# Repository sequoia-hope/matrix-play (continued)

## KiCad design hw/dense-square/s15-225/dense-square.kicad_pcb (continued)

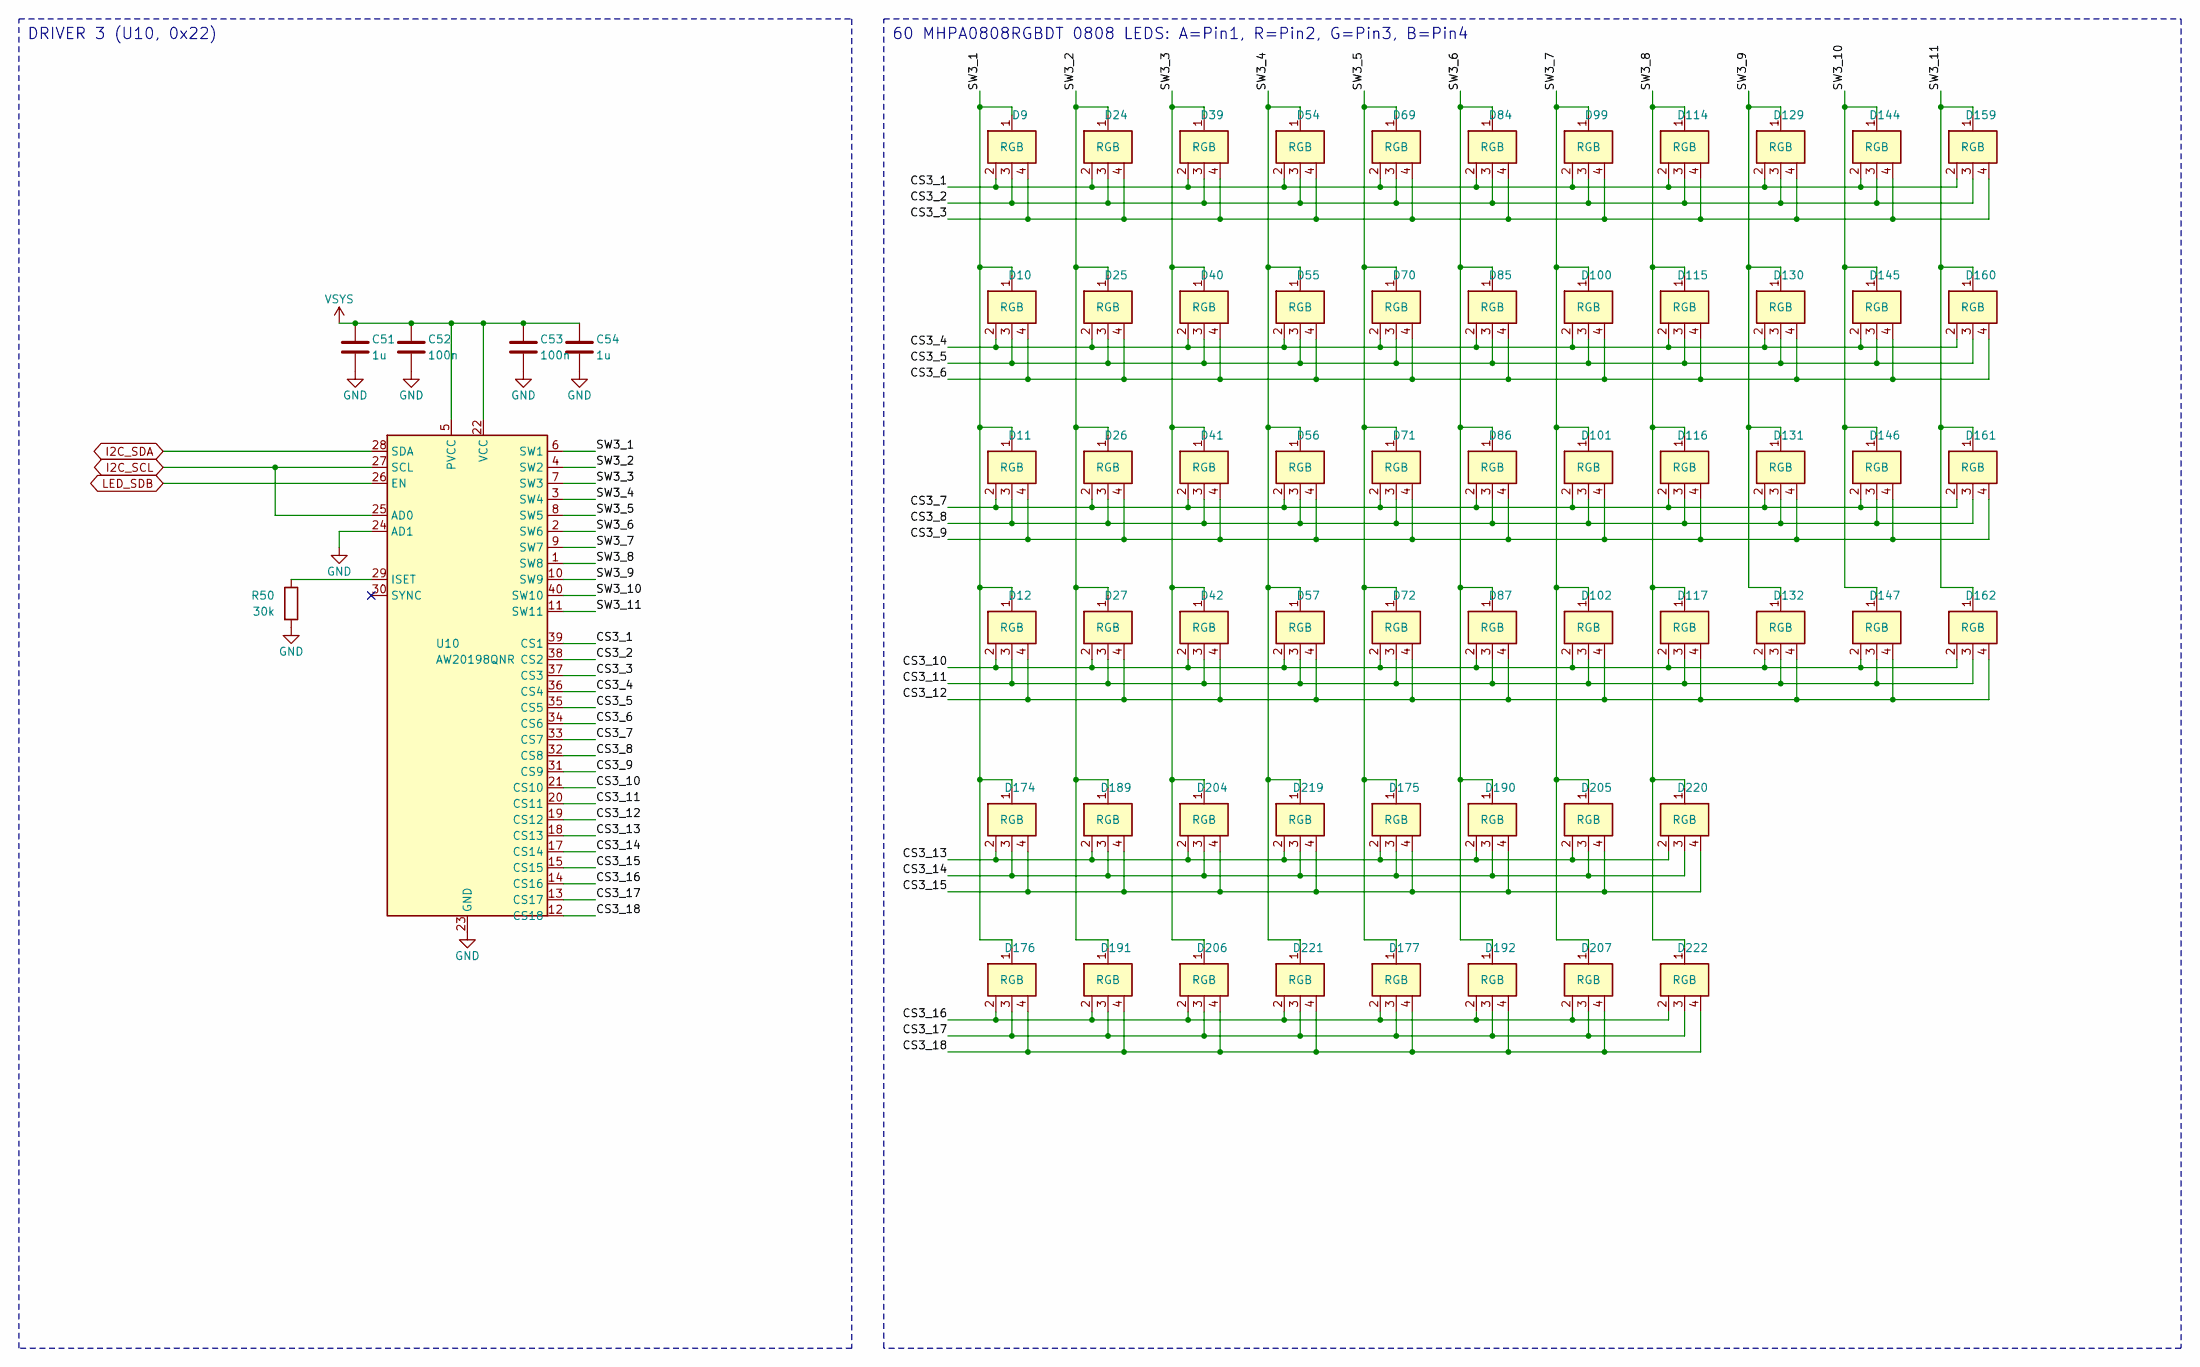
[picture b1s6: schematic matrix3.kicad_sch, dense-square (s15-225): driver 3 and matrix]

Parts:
C51, C54: 1u; C_0402_1005Metric; MPN CL05A105KA5NQNC; LCSC C52923
C52, C53: 100n; C_0402_1005Metric; MPN CL05B104KO5NNNC; LCSC C1525
D9, D10, D11, D12, D24, D25, D26, D27, D39, D40, D41, D42, D54, D55, D56, D57, D69, D70, D71, D72, D84, D85, D86, D87, D99, D100, D101, D102, D114, D115, D116, D117, D129, D130, D131, D132, D144, D145, D146, D147, D159, D160, D161, D162, D174, D175, D176, D177, D189, D190, D191, D192, D204, D205, D206, D207, D219, D220, D221, D222: RGB; LED_MHPA0808RGBDT; MPN MHPA0808RGBDT; LCSC C404279
R50: 30k; R_0402_1005Metric; MPN 0402WGF3002TCE; LCSC C25776
U10: AW20198QNR; AW20198_QFN-40-1EP_5x5mm_P0.4mm_EP3.4x3.4mm; MPN AW20198QNR; LCSC C5137654

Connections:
/Driver 3 and matrix/CS3_1: D9.2 (R), D24.2 (R), D39.2 (R), D54.2 (R), D69.2 (R), D84.2 (R), D99.2 (R), D114.2 (R), D129.2 (R), D144.2 (R), D159.2 (R), U10.39 (CS1)
/Driver 3 and matrix/CS3_2: D9.3 (G), D24.3 (G), D39.3 (G), D54.3 (G), D69.3 (G), D84.3 (G), D99.3 (G), D114.3 (G), D129.3 (G), D144.3 (G), D159.3 (G), U10.38 (CS2)
/Driver 3 and matrix/CS3_3: D9.4 (B), D24.4 (B), D39.4 (B), D54.4 (B), D69.4 (B), D84.4 (B), D99.4 (B), D114.4 (B), D129.4 (B), D144.4 (B), D159.4 (B), U10.37 (CS3)
/Driver 3 and matrix/CS3_4: D10.2 (R), D25.2 (R), D40.2 (R), D55.2 (R), D70.2 (R), D85.2 (R), D100.2 (R), D115.2 (R), D130.2 (R), D145.2 (R), D160.2 (R), U10.36 (CS4)
/Driver 3 and matrix/CS3_5: D10.3 (G), D25.3 (G), D40.3 (G), D55.3 (G), D70.3 (G), D85.3 (G), D100.3 (G), D115.3 (G), D130.3 (G), D145.3 (G), D160.3 (G), U10.35 (CS5)
/Driver 3 and matrix/CS3_6: D10.4 (B), D25.4 (B), D40.4 (B), D55.4 (B), D70.4 (B), D85.4 (B), D100.4 (B), D115.4 (B), D130.4 (B), D145.4 (B), D160.4 (B), U10.34 (CS6)
/Driver 3 and matrix/CS3_7: D11.2 (R), D26.2 (R), D41.2 (R), D56.2 (R), D71.2 (R), D86.2 (R), D101.2 (R), D116.2 (R), D131.2 (R), D146.2 (R), D161.2 (R), U10.33 (CS7)
/Driver 3 and matrix/CS3_8: D11.3 (G), D26.3 (G), D41.3 (G), D56.3 (G), D71.3 (G), D86.3 (G), D101.3 (G), D116.3 (G), D131.3 (G), D146.3 (G), D161.3 (G), U10.32 (CS8)
/Driver 3 and matrix/CS3_9: D11.4 (B), D26.4 (B), D41.4 (B), D56.4 (B), D71.4 (B), D86.4 (B), D101.4 (B), D116.4 (B), D131.4 (B), D146.4 (B), D161.4 (B), U10.31 (CS9)
/Driver 3 and matrix/CS3_10: D12.2 (R), D27.2 (R), D42.2 (R), D57.2 (R), D72.2 (R), D87.2 (R), D102.2 (R), D117.2 (R), D132.2 (R), D147.2 (R), D162.2 (R), U10.21 (CS10)
/Driver 3 and matrix/CS3_11: D12.3 (G), D27.3 (G), D42.3 (G), D57.3 (G), D72.3 (G), D87.3 (G), D102.3 (G), D117.3 (G), D132.3 (G), D147.3 (G), D162.3 (G), U10.20 (CS11)
/Driver 3 and matrix/CS3_12: D12.4 (B), D27.4 (B), D42.4 (B), D57.4 (B), D72.4 (B), D87.4 (B), D102.4 (B), D117.4 (B), D132.4 (B), D147.4 (B), D162.4 (B), U10.19 (CS12)
/Driver 3 and matrix/CS3_13: D174.2 (R), D175.2 (R), D189.2 (R), D190.2 (R), D204.2 (R), D205.2 (R), D219.2 (R), D220.2 (R), U10.18 (CS13)
/Driver 3 and matrix/CS3_14: D174.3 (G), D175.3 (G), D189.3 (G), D190.3 (G), D204.3 (G), D205.3 (G), D219.3 (G), D220.3 (G), U10.17 (CS14)
/Driver 3 and matrix/CS3_15: D174.4 (B), D175.4 (B), D189.4 (B), D190.4 (B), D204.4 (B), D205.4 (B), D219.4 (B), D220.4 (B), U10.15 (CS15)
/Driver 3 and matrix/CS3_16: D176.2 (R), D177.2 (R), D191.2 (R), D192.2 (R), D206.2 (R), D207.2 (R), D221.2 (R), D222.2 (R), U10.14 (CS16)
/Driver 3 and matrix/CS3_17: D176.3 (G), D177.3 (G), D191.3 (G), D192.3 (G), D206.3 (G), D207.3 (G), D221.3 (G), D222.3 (G), U10.13 (CS17)
/Driver 3 and matrix/CS3_18: D176.4 (B), D177.4 (B), D191.4 (B), D192.4 (B), D206.4 (B), D207.4 (B), D221.4 (B), D222.4 (B), U10.12 (CS18)
/Driver 3 and matrix/SW3_1: D9.1 (A), D10.1 (A), D11.1 (A), D12.1 (A), D174.1 (A), D176.1 (A), U10.6 (SW1)
/Driver 3 and matrix/SW3_2: D24.1 (A), D25.1 (A), D26.1 (A), D27.1 (A), D189.1 (A), D191.1 (A), U10.4 (SW2)
/Driver 3 and matrix/SW3_3: D39.1 (A), D40.1 (A), D41.1 (A), D42.1 (A), D204.1 (A), D206.1 (A), U10.7 (SW3)
/Driver 3 and matrix/SW3_4: D54.1 (A), D55.1 (A), D56.1 (A), D57.1 (A), D219.1 (A), D221.1 (A), U10.3 (SW4)
/Driver 3 and matrix/SW3_5: D69.1 (A), D70.1 (A), D71.1 (A), D72.1 (A), D175.1 (A), D177.1 (A), U10.8 (SW5)
/Driver 3 and matrix/SW3_6: D84.1 (A), D85.1 (A), D86.1 (A), D87.1 (A), D190.1 (A), D192.1 (A), U10.2 (SW6)
/Driver 3 and matrix/SW3_7: D99.1 (A), D100.1 (A), D101.1 (A), D102.1 (A), D205.1 (A), D207.1 (A), U10.9 (SW7)
/Driver 3 and matrix/SW3_8: D114.1 (A), D115.1 (A), D116.1 (A), D117.1 (A), D220.1 (A), D222.1 (A), U10.1 (SW8)
/Driver 3 and matrix/SW3_9: D129.1 (A), D130.1 (A), D131.1 (A), D132.1 (A), U10.10 (SW9)
/Driver 3 and matrix/SW3_10: D144.1 (A), D145.1 (A), D146.1 (A), D147.1 (A), U10.40 (SW10)
/Driver 3 and matrix/SW3_11: D159.1 (A), D160.1 (A), D161.1 (A), D162.1 (A), U10.11 (SW11)
I2C_SCL: U10.25 (AD0), U10.27 (SCL); also elsewhere on the board
I2C_SDA: U10.28 (SDA); also elsewhere on the board
LED_SDB: U10.26 (EN); also elsewhere on the board
unnamed: R50.1, U10.29 (ISET)
VSYS: C51.1, C52.1, C53.1, C54.1, U10.5 (PVCC), U10.22 (VCC); also elsewhere on the board

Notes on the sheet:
DRIVER 3 (U10, 0x22)
60 MHPA0808RGBDT 0808 LEDS: A=Pin1, R=Pin2, G=Pin3, B=Pin4

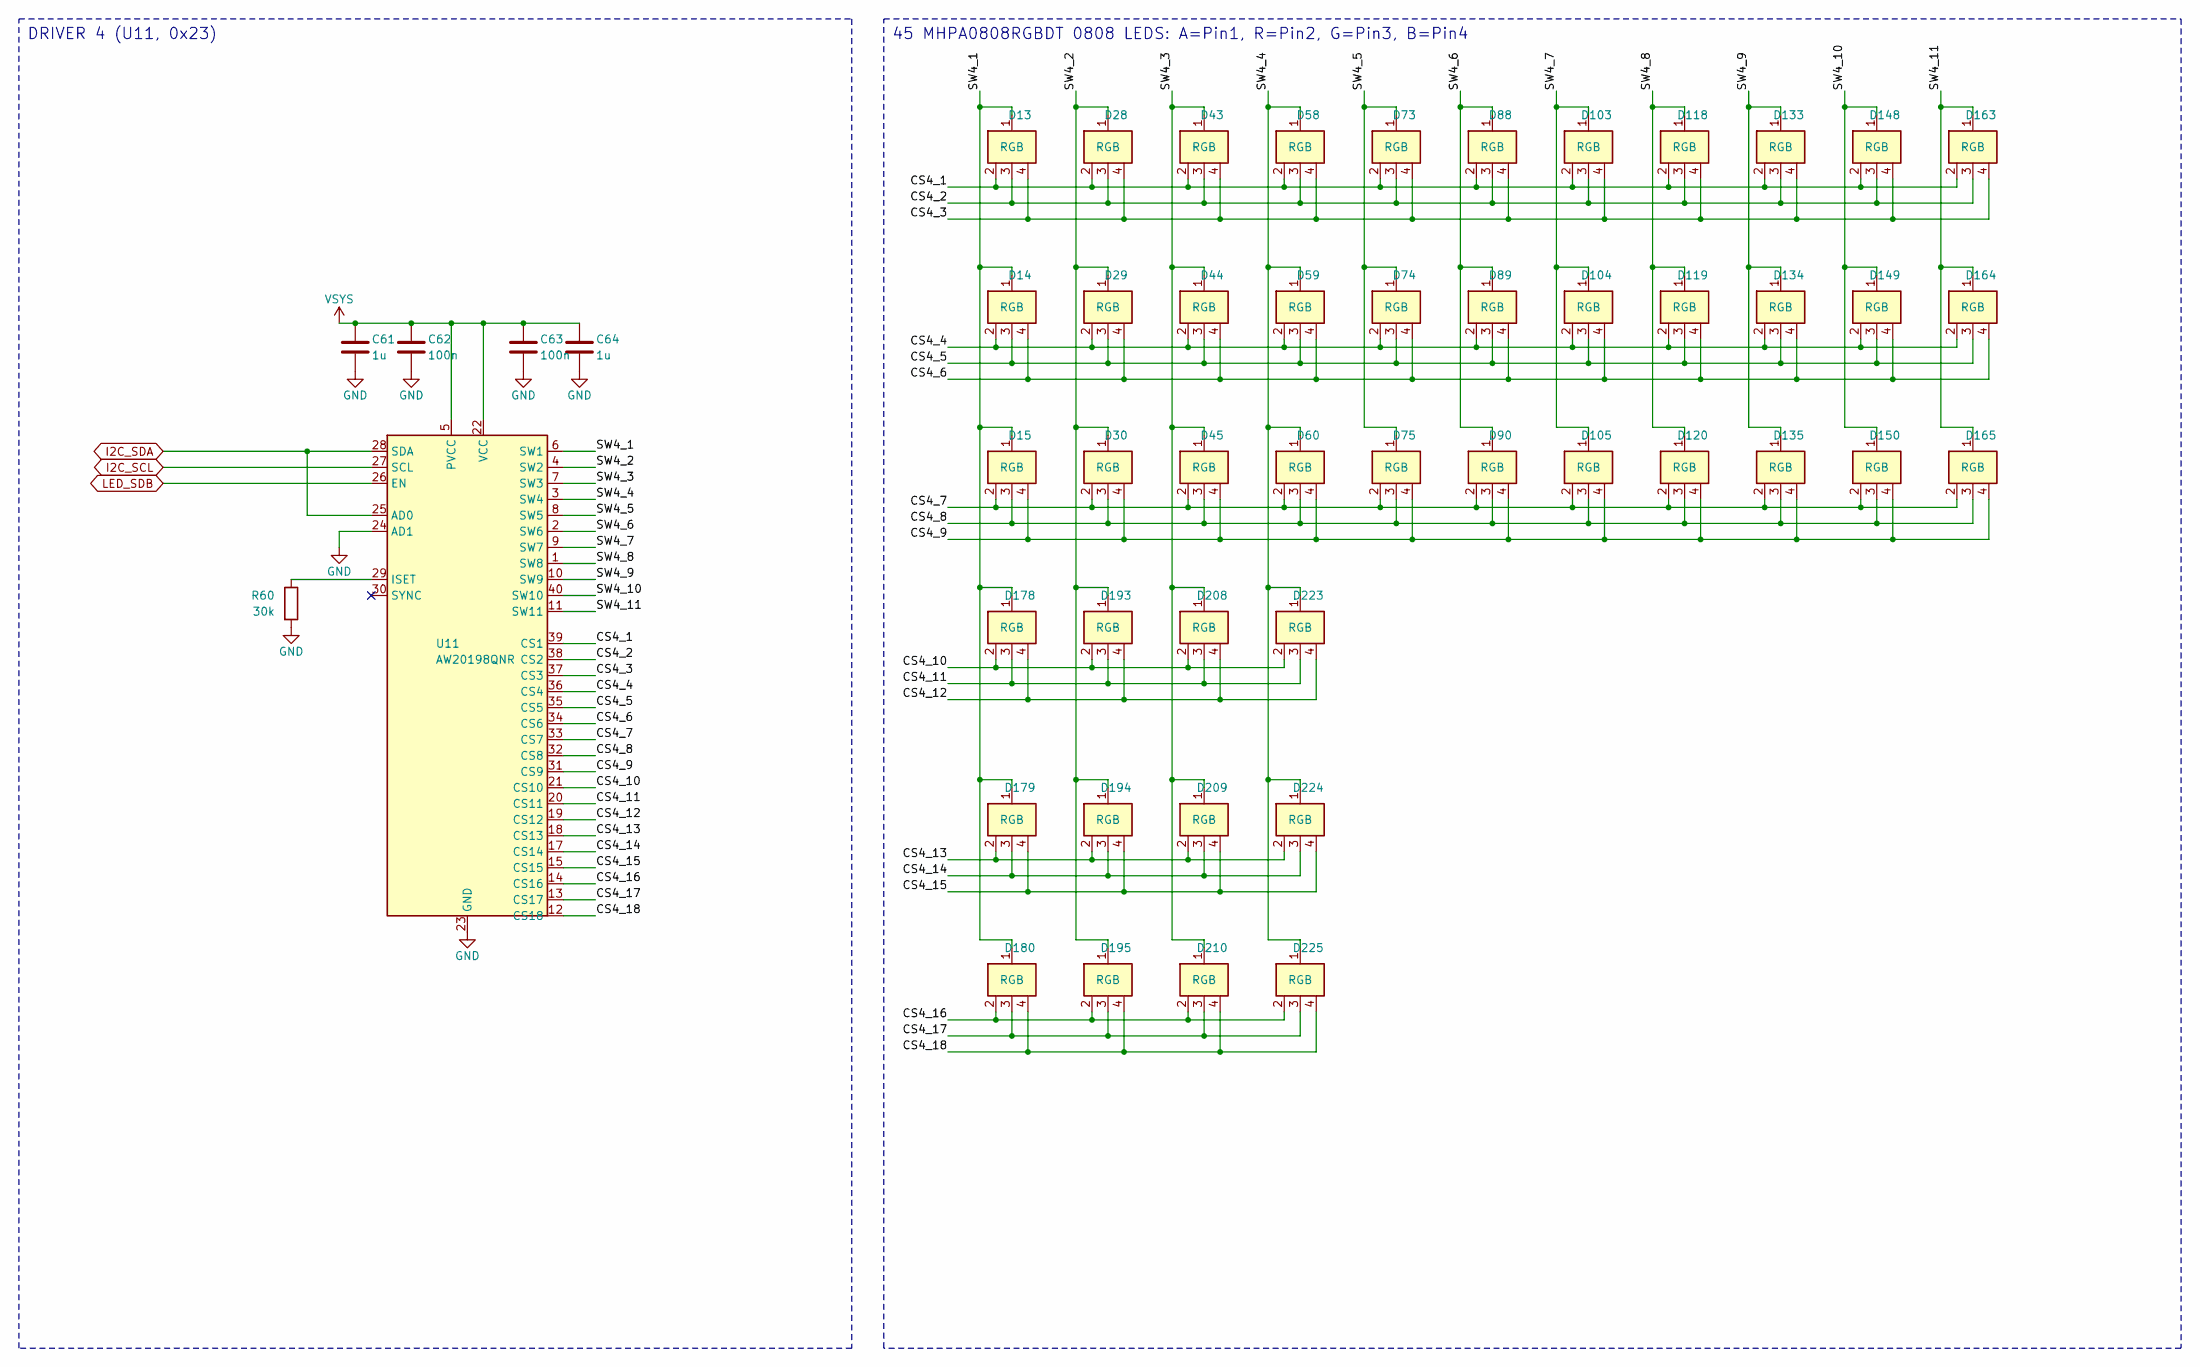
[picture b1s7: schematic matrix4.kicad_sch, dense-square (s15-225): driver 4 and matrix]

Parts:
C61, C64: 1u; C_0402_1005Metric; MPN CL05A105KA5NQNC; LCSC C52923
C62, C63: 100n; C_0402_1005Metric; MPN CL05B104KO5NNNC; LCSC C1525
D13, D14, D15, D28, D29, D30, D43, D44, D45, D58, D59, D60, D73, D74, D75, D88, D89, D90, D103, D104, D105, D118, D119, D120, D133, D134, D135, D148, D149, D150, D163, D164, D165, D178, D179, D180, D193, D194, D195, D208, D209, D210, D223, D224, D225: RGB; LED_MHPA0808RGBDT; MPN MHPA0808RGBDT; LCSC C404279
R60: 30k; R_0402_1005Metric; MPN 0402WGF3002TCE; LCSC C25776
U11: AW20198QNR; AW20198_QFN-40-1EP_5x5mm_P0.4mm_EP3.4x3.4mm; MPN AW20198QNR; LCSC C5137654

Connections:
/Driver 4 and matrix/CS4_1: D13.2 (R), D28.2 (R), D43.2 (R), D58.2 (R), D73.2 (R), D88.2 (R), D103.2 (R), D118.2 (R), D133.2 (R), D148.2 (R), D163.2 (R), U11.39 (CS1)
/Driver 4 and matrix/CS4_2: D13.3 (G), D28.3 (G), D43.3 (G), D58.3 (G), D73.3 (G), D88.3 (G), D103.3 (G), D118.3 (G), D133.3 (G), D148.3 (G), D163.3 (G), U11.38 (CS2)
/Driver 4 and matrix/CS4_3: D13.4 (B), D28.4 (B), D43.4 (B), D58.4 (B), D73.4 (B), D88.4 (B), D103.4 (B), D118.4 (B), D133.4 (B), D148.4 (B), D163.4 (B), U11.37 (CS3)
/Driver 4 and matrix/CS4_4: D14.2 (R), D29.2 (R), D44.2 (R), D59.2 (R), D74.2 (R), D89.2 (R), D104.2 (R), D119.2 (R), D134.2 (R), D149.2 (R), D164.2 (R), U11.36 (CS4)
/Driver 4 and matrix/CS4_5: D14.3 (G), D29.3 (G), D44.3 (G), D59.3 (G), D74.3 (G), D89.3 (G), D104.3 (G), D119.3 (G), D134.3 (G), D149.3 (G), D164.3 (G), U11.35 (CS5)
/Driver 4 and matrix/CS4_6: D14.4 (B), D29.4 (B), D44.4 (B), D59.4 (B), D74.4 (B), D89.4 (B), D104.4 (B), D119.4 (B), D134.4 (B), D149.4 (B), D164.4 (B), U11.34 (CS6)
/Driver 4 and matrix/CS4_7: D15.2 (R), D30.2 (R), D45.2 (R), D60.2 (R), D75.2 (R), D90.2 (R), D105.2 (R), D120.2 (R), D135.2 (R), D150.2 (R), D165.2 (R), U11.33 (CS7)
/Driver 4 and matrix/CS4_8: D15.3 (G), D30.3 (G), D45.3 (G), D60.3 (G), D75.3 (G), D90.3 (G), D105.3 (G), D120.3 (G), D135.3 (G), D150.3 (G), D165.3 (G), U11.32 (CS8)
/Driver 4 and matrix/CS4_9: D15.4 (B), D30.4 (B), D45.4 (B), D60.4 (B), D75.4 (B), D90.4 (B), D105.4 (B), D120.4 (B), D135.4 (B), D150.4 (B), D165.4 (B), U11.31 (CS9)
/Driver 4 and matrix/CS4_10: D178.2 (R), D193.2 (R), D208.2 (R), D223.2 (R), U11.21 (CS10)
/Driver 4 and matrix/CS4_11: D178.3 (G), D193.3 (G), D208.3 (G), D223.3 (G), U11.20 (CS11)
/Driver 4 and matrix/CS4_12: D178.4 (B), D193.4 (B), D208.4 (B), D223.4 (B), U11.19 (CS12)
/Driver 4 and matrix/CS4_13: D179.2 (R), D194.2 (R), D209.2 (R), D224.2 (R), U11.18 (CS13)
/Driver 4 and matrix/CS4_14: D179.3 (G), D194.3 (G), D209.3 (G), D224.3 (G), U11.17 (CS14)
/Driver 4 and matrix/CS4_15: D179.4 (B), D194.4 (B), D209.4 (B), D224.4 (B), U11.15 (CS15)
/Driver 4 and matrix/CS4_16: D180.2 (R), D195.2 (R), D210.2 (R), D225.2 (R), U11.14 (CS16)
/Driver 4 and matrix/CS4_17: D180.3 (G), D195.3 (G), D210.3 (G), D225.3 (G), U11.13 (CS17)
/Driver 4 and matrix/CS4_18: D180.4 (B), D195.4 (B), D210.4 (B), D225.4 (B), U11.12 (CS18)
/Driver 4 and matrix/SW4_1: D13.1 (A), D14.1 (A), D15.1 (A), D178.1 (A), D179.1 (A), D180.1 (A), U11.6 (SW1)
/Driver 4 and matrix/SW4_2: D28.1 (A), D29.1 (A), D30.1 (A), D193.1 (A), D194.1 (A), D195.1 (A), U11.4 (SW2)
/Driver 4 and matrix/SW4_3: D43.1 (A), D44.1 (A), D45.1 (A), D208.1 (A), D209.1 (A), D210.1 (A), U11.7 (SW3)
/Driver 4 and matrix/SW4_4: D58.1 (A), D59.1 (A), D60.1 (A), D223.1 (A), D224.1 (A), D225.1 (A), U11.3 (SW4)
/Driver 4 and matrix/SW4_5: D73.1 (A), D74.1 (A), D75.1 (A), U11.8 (SW5)
/Driver 4 and matrix/SW4_6: D88.1 (A), D89.1 (A), D90.1 (A), U11.2 (SW6)
/Driver 4 and matrix/SW4_7: D103.1 (A), D104.1 (A), D105.1 (A), U11.9 (SW7)
/Driver 4 and matrix/SW4_8: D118.1 (A), D119.1 (A), D120.1 (A), U11.1 (SW8)
/Driver 4 and matrix/SW4_9: D133.1 (A), D134.1 (A), D135.1 (A), U11.10 (SW9)
/Driver 4 and matrix/SW4_10: D148.1 (A), D149.1 (A), D150.1 (A), U11.40 (SW10)
/Driver 4 and matrix/SW4_11: D163.1 (A), D164.1 (A), D165.1 (A), U11.11 (SW11)
I2C_SCL: U11.27 (SCL); also elsewhere on the board
I2C_SDA: U11.25 (AD0), U11.28 (SDA); also elsewhere on the board
LED_SDB: U11.26 (EN); also elsewhere on the board
unnamed: R60.1, U11.29 (ISET)
VSYS: C61.1, C62.1, C63.1, C64.1, U11.5 (PVCC), U11.22 (VCC); also elsewhere on the board

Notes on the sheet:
DRIVER 4 (U11, 0x23)
45 MHPA0808RGBDT 0808 LEDS: A=Pin1, R=Pin2, G=Pin3, B=Pin4

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
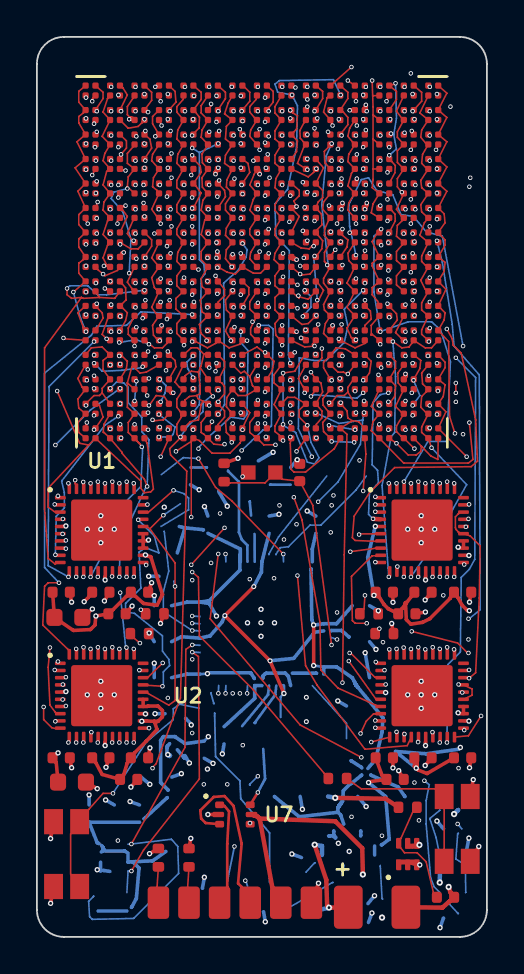
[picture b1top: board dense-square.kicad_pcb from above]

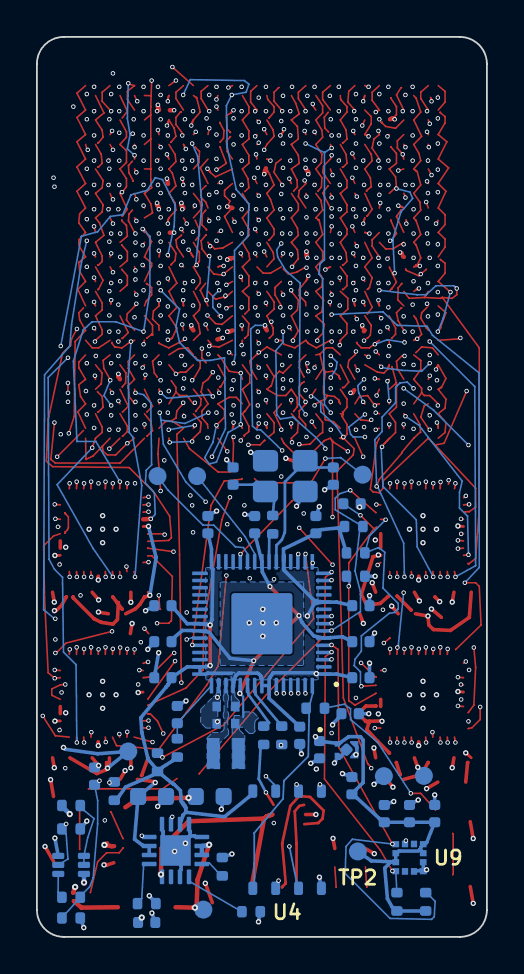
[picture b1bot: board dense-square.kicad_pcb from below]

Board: 8 copper layers, 25.0 x 50.0 mm, 326 parts (61 on the bottom side), 170 nets.

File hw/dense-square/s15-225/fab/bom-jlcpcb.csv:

Comment,Designator,Footprint,LCSC Part #,MPN,Manufacturer
1u,"C1,C3,C4,C31,C34,C41,C44,C51,C54,C61,C64",C_0402_1005Metric,C52923,CL05A105KA5NQNC,Samsung Electro-Mechanics
22u,"C2,C30,C40",C_0603_1608Metric,C86295,CL10A226MP8NUNE,Samsung Electro-Mechanics
10u,C5,C_0603_1608Metric,C19702,CL10A106KP8NNNC,Samsung Electro-Mechanics
100n,"C6,C7,C8,C9,C10,C11,C12,C13,C14,C20,C21,C22,C25,C27,C32,C33,C35,C42,C43,C52,C53,C62,C63,C70",C_0402_1005Metric,C1525,CL05B104KO5NNNC,Samsung Electro-Mechanics
4.7u,"C16,C18",C_0402_1005Metric_small_pads,C23733,CL05A475MP5NRNC,Samsung Electro-Mechanics
4.7u,"C17,C19,C26",C_0402_1005Metric,C23733,CL05A475MP5NRNC,Samsung Electro-Mechanics
15p,"C23,C24",C_0402_1005Metric,C1548,0402CG150J500NT,FH
RGB,"D1,D2,D3,D4,D5,D6,D7,D8,D9,D10,D11,D12,D13,D14,D15,D16,D17,D18,D19,D20,D21,D22,D23,D24,D25,D26,D27,D28,D29,D30,D31,D32,D33,D34,D35,D36,D37,D38,D39,D40,D41,D42,D43,D44,D45,D46,D47,D48,D49,D50,D51,D52,D53,D54,D55,D56,D57,D58,D59,D60,D61,D62,D63,D64,D65,D66,D67,D68,D69,D70,D71,D72,D73,D74,D75,D76,D77,D78,D79,D80,D81,D82,D83,D84,D85,D86,D87,D88,D89,D90,D91,D92,D93,D94,D95,D96,D97,D98,D99,D100,D101,D102,D103,D104,D105,D106,D107,D108,D109,D110,D111,D112,D113,D114,D115,D116,D117,D118,D119,D120,D121,D122,D123,D124,D125,D126,D127,D128,D129,D130,D131,D132,D133,D134,D135,D136,D137,D138,D139,D140,D141,D142,D143,D144,D145,D146,D147,D148,D149,D150,D151,D152,D153,D154,D155,D156,D157,D158,D159,D160,D161,D162,D163,D164,D165,D166,D167,D168,D169,D170,D171,D172,D173,D174,D175,D176,D177,D178,D179,D180,D181,D182,D183,D184,D185,D186,D187,D188,D189,D190,D191,D192,D193,D194,D195,D196,D197,D198,D199,D200,D201,D202,D203,D204,D205,D206,D207,D208,D209,D210,D211,D212,D213,D214,D215,D216,D217,D218,D219,D220,D221,D222,D223,D224,D225",LED_MHPA0808RGBDT,C404279,MHPA0808RGBDT,MEIHUA
3.3u,L1,L_pol_2016,C42411119,AOTA-B201610S3R3-101-T,Abracon
NTZD3155C,Q1,SOT-563,C236117,NTZD3155CT1G,onsemi
XYC-PT19C-L1,Q2,SENSOR_ALS-PT19,C2693594,XYC-PT19C-L1,NEWOPTO
5.1k,"R1,R2",R_0402_1005Metric,C25905,0402WGF5101TCE,UNI-ROYAL
10k,R3,R_0402_1005Metric,C25744,0402WGF1002TCE,UNI-ROYAL
3k,R4,R_0402_1005Metric,C25784,0402WGF3001TCE,UNI-ROYAL
3.6k,R5,R_0402_1005Metric,C25891,0402WGF3601TCE,UNI-ROYAL
100k,"R6,R7,R9,R10,R11,R12,R31",R_0402_1005Metric,C25741,0402WGF1003TCE,UNI-ROYAL
100R,R8,R_0402_1005Metric,C25076,0402WGF1000TCE,UNI-ROYAL
33R,R13,R_0402_1005Metric,C25105,0402WGF330JTCE,UNI-ROYAL
27R,"R14,R15",R_0402_1005Metric,C25100,0402WGF270JTCE,UNI-ROYAL
1k,"R16,R17,R18,R21,R22",R_0402_1005Metric,C11702,0402WGF1001TCE,UNI-ROYAL
4.7k,"R19,R20",R_0402_1005Metric,C25900,0402WGF4701TCE,UNI-ROYAL
30k,"R30,R33,R50,R60",R_0402_1005Metric,C25776,0402WGF3002TCE,UNI-ROYAL
22k,R43,R_0402_1005Metric,C25768,0402WGF2202TCE,UNI-ROYAL
USER / WAKE,SW1,SW_Panasonic_EVQP7J,C2828254,EVQP7J01P,PANASONIC
BOOTSEL,SW2,SW_Panasonic_EVQP7J,C2828254,EVQP7J01P,PANASONIC
AW20198QNR,"U1,U2,U10,U11",AW20198_QFN-40-1EP_5x5mm_P0.4mm_EP3.4x3.4mm,C5137654,AW20198QNR,Shanghai Awinic Tech
RP2350A,U3,RP2350-QFN-60-1EP_7x7_P0.4mm_EP3.4x3.4mm_ThermalVias,C42411118,RP2350A,Raspberry Pi
W25Q128JVPIQ,U4,WSON-8_6x5mm_P1.27mm_NoEPCopper,C190862,W25Q128JVPIQ,Winbond
BQ24073,U5,QFN-16-1EP_3x3mm_P0.5mm_EP1.7x1.7mm,C15220,BQ24073RGTR,Texas Instruments
TPS7A0233,U6,Texas_X2SON-4_1x1mm_P0.65mm,C2860046,TPS7A0233PDQNR,Texas Instruments
USBLC6-2P6,U7,SOT-666,C15999,USBLC6-2P6,STMicroelectronics
XB9901A,U8,XySemi_DFN-6_1.8x1.4mm,C669687,XB9901A,XySemi
LIS2DW12,U9,LGA-12_2x2mm_P0.5mm,C189624,LIS2DW12TR,STMicroelectronics
12MHz,Y1,Crystal_SMD_3225-4Pin_3.2x2.5mm,C20625731,ABM8-272-T3,Abracon

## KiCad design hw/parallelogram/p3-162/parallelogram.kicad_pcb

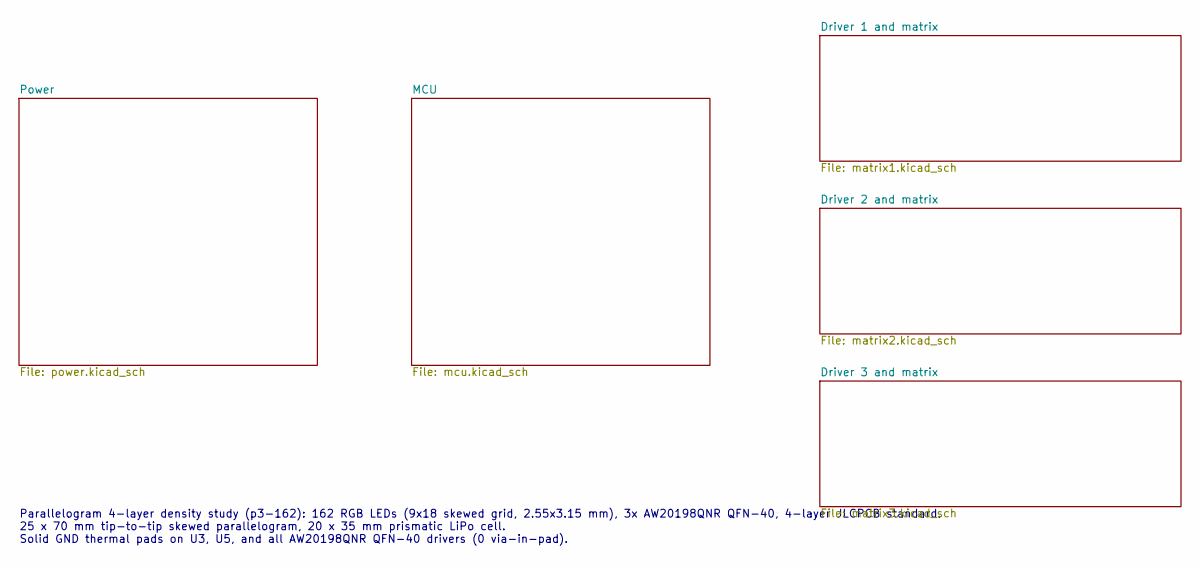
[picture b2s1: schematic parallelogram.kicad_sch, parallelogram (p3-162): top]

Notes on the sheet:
Parallelogram 4-layer density study (p3-162): 162 RGB LEDs (9x18 skewed grid, 2.55x3.15 mm), 3x AW20198QNR QFN-40, 4-layer JLCPCB standard. 25 x 70 mm tip-to-tip skewed parallelogram, 20 x 35 mm prismatic LiPo cell. Solid GND thermal pads on U3, U5, and all AW20198QNR QFN-40 drivers (0 via-in-pad).

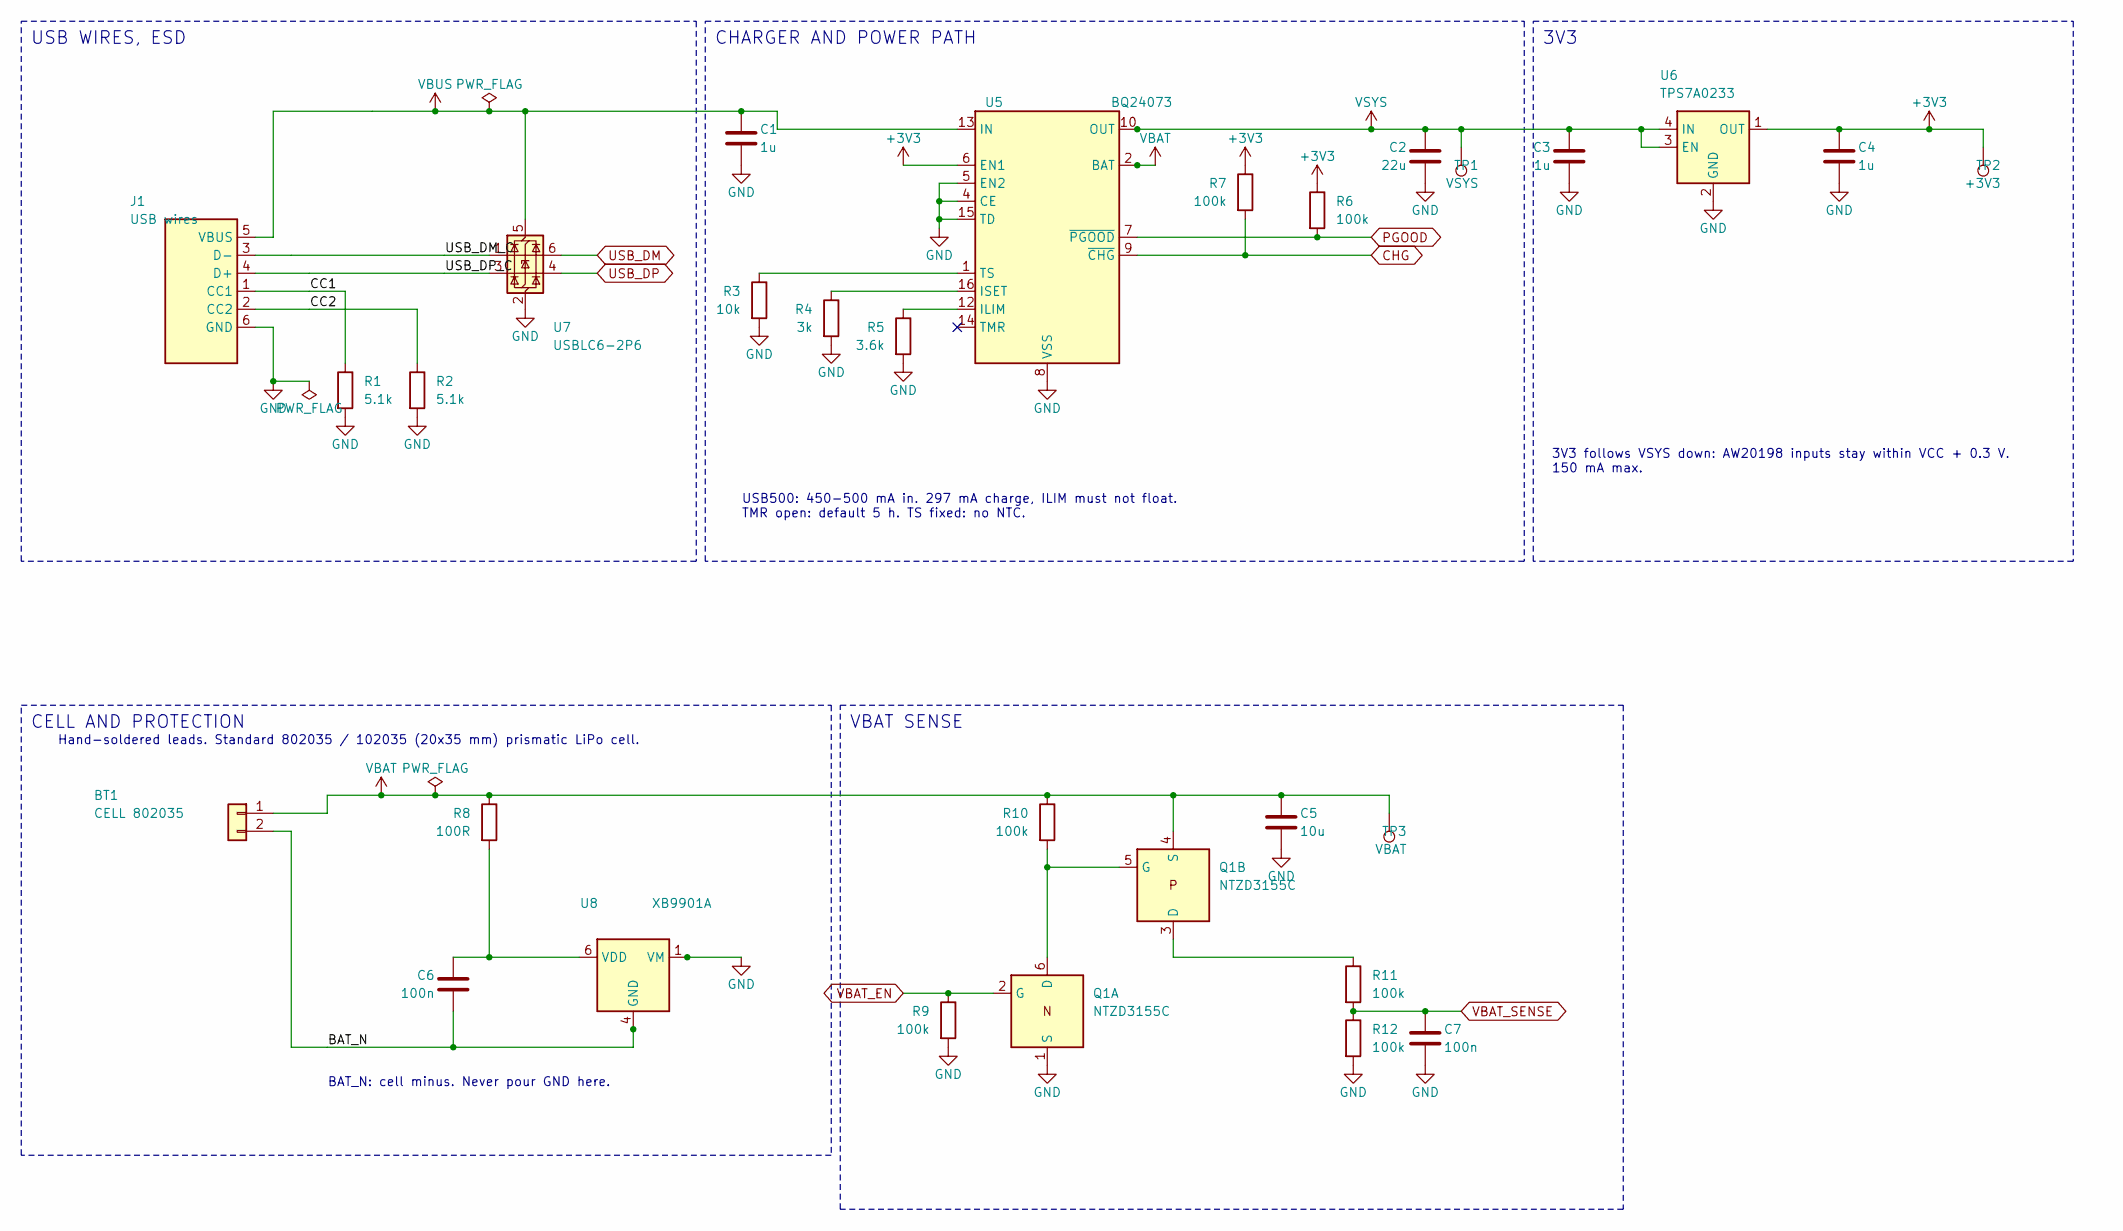
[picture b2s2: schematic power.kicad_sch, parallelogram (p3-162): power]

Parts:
BT1: CELL 802035; BatteryPads; MPN 802035
C1, C3, C4: 1u; C_0402_1005Metric; MPN CL05A105KA5NQNC; LCSC C52923
C2: 22u; C_0603_1608Metric; MPN CL10A226MP8NUNE; LCSC C86295
C5: 10u; C_0603_1608Metric; MPN CL10A106KP8NNNC; LCSC C19702
C6, C7: 100n; C_0402_1005Metric; MPN CL05B104KO5NNNC; LCSC C1525
J1: USB wires; USB_Pads; MPN none, wire pads
Q1: NTZD3155C; SOT-563; MPN NTZD3155CT1G; LCSC C236117
R1, R2: 5.1k; R_0402_1005Metric; MPN 0402WGF5101TCE; LCSC C25905
R3: 10k; R_0402_1005Metric; MPN 0402WGF1002TCE; LCSC C25744
R4: 3k; R_0402_1005Metric; MPN 0402WGF3001TCE; LCSC C25784
R5: 3.6k; R_0402_1005Metric; MPN 0402WGF3601TCE; LCSC C25891
R6, R7, R9, R10, R11, R12: 100k; R_0402_1005Metric; MPN 0402WGF1003TCE; LCSC C25741
R8: 100R; R_0402_1005Metric; MPN 0402WGF1000TCE; LCSC C25076
TP1: VSYS; TestPoint_Pad_D1.0mm
TP2: +3V3; TestPoint_Pad_D1.0mm
TP3: VBAT; TestPoint_Pad_D1.0mm
U5: BQ24073; QFN-16-1EP_3x3mm_P0.5mm_EP1.7x1.7mm; MPN BQ24073RGTR; LCSC C15220
U6: TPS7A0233; Texas_X2SON-4_1x1mm_P0.65mm; MPN TPS7A0233PDQNR; LCSC C2860046
U7: USBLC6-2P6; SOT-666; MPN USBLC6-2P6; LCSC C15999
U8: XB9901A; XySemi_DFN-6_1.8x1.4mm; MPN XB9901A; LCSC C669687

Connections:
+3V3: C4.1, R6.1, R7.1, TP2.1, U5.6 (EN1), U6.1 (OUT); also elsewhere on the board
/Power/BAT_N: BT1.2, C6.2, U8.4 (GND), U8.5 (GND)
/Power/CC1: J1.1 (CC1), R1.1
/Power/CC2: J1.2 (CC2), R2.1
/Power/USB_DM_C: J1.3 (D-), U7.1 (I/O1)
/Power/USB_DP_C: J1.4 (D+), U7.3 (I/O2)
CHG: R7.2, U5.9 (~CHG); also elsewhere on the board
unnamed: Q1.5 (G), Q1.6 (D), R10.2
unnamed: Q1.3 (D), R11.1
unnamed: R5.1, U5.12 (ILIM)
unnamed: R4.1, U5.16 (ISET)
unnamed: R3.1, U5.1 (TS)
unnamed: C6.1, R8.2, U8.6 (VDD)
PGOOD: R6.2, U5.7 (~PGOOD); also elsewhere on the board
USB_DM: U7.6 (I/O1); also elsewhere on the board
USB_DP: U7.4 (I/O2); also elsewhere on the board
VBAT_EN: Q1.2 (G), R9.1; also elsewhere on the board
VBAT_SENSE: C7.1, R11.2, R12.1; also elsewhere on the board
VSYS: C2.1, C3.1, TP1.1, U5.10 (OUT), U5.11 (OUT), U6.3 (EN), U6.4 (IN); also elsewhere on the board

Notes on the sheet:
USB WIRES, ESD
USB500: 450-500 mA in. 297 mA charge, ILIM must not float. TMR open: default 5 h. TS fixed: no NTC.
CHARGER AND POWER PATH
3V3 follows VSYS down: AW20198 inputs stay within VCC + 0.3 V. 150 mA max.
3V3
Hand-soldered leads. Standard 802035 / 102035 (20x35 mm) prismatic LiPo cell.
BAT_N: cell minus. Never pour GND here.
CELL AND PROTECTION
VBAT SENSE
